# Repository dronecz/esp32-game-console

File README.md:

# ESP32 game console 

You can read more about my project [here](https://hackaday.io/project/166873-esp32-game-console) at Hackaday.io . :slightly_smiling_face:

This repository contain PCB files and 3D files for ESP32 game console. 

In case that you will have any question, you can contact me at info@czechmaker.com

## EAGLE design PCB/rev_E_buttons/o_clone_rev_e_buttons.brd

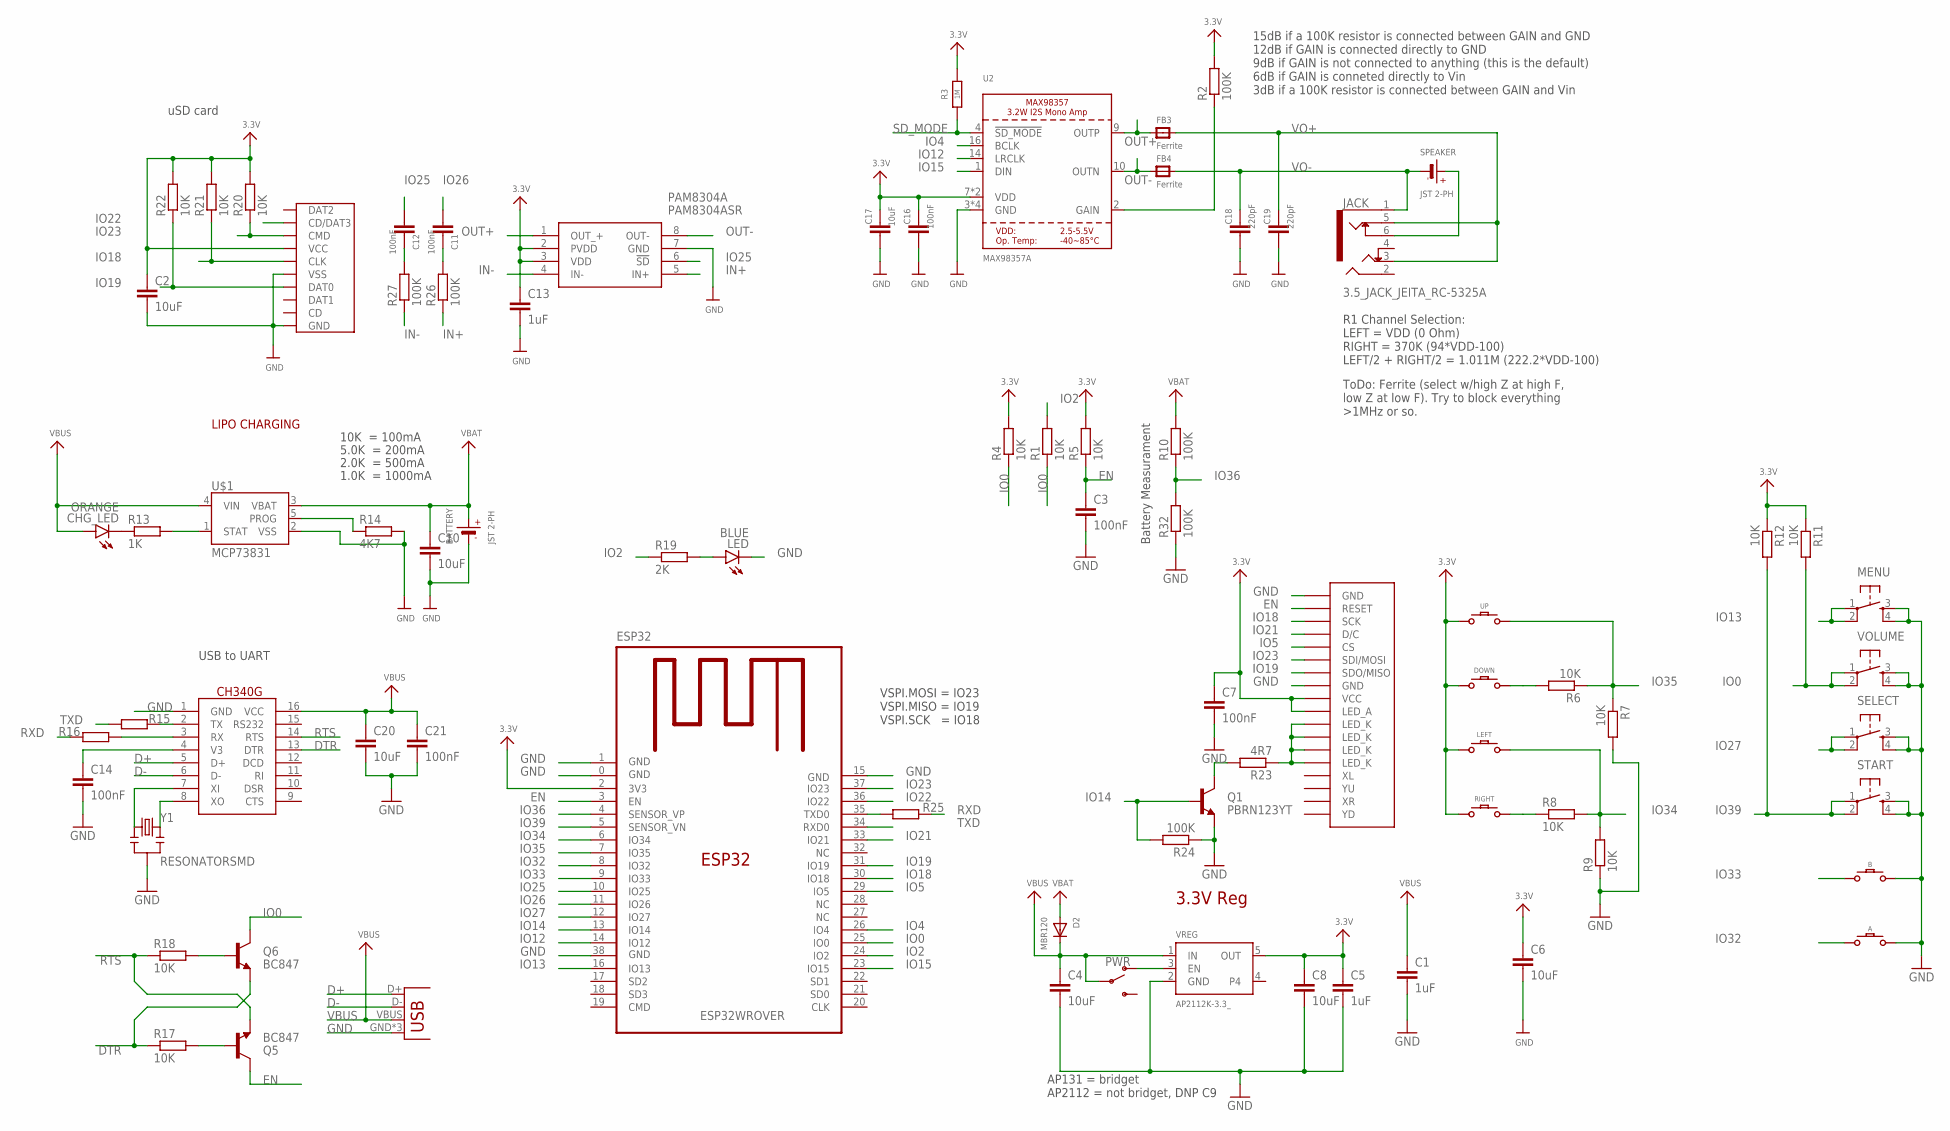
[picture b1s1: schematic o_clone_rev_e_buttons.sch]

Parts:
A: CONDUCTIVE_BUTTONCONDUCTIVE_BUTTON_THICK; CONDUCTIVE_BUTTON_THICK
B: CONDUCTIVE_BUTTONCONDUCTIVE_BUTTON_THICK; CONDUCTIVE_BUTTON_THICK
BATTERY: JST 2-PH; JSTPH2
C1, C5, C13: 1uF; C0805K
C2, C4, C6, C8, C10, C17, C20: 10uF; C0805K
C3, C11, C12, C14, C16, C21: 100nF; C0805K
C7: 100nF; C0805
C18, C19: 220pF; C0805K
CHG_LED: ORANGE; CHIPLED_0805
D2: MBR120; SOD-123
DOWN: CONDUCTIVE_BUTTONCONDUCTIVE_BUTTON_DIRECTIONAL_TH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; CONDUCTIVE_BUTTON_DIRECTIONAL_THICK
ESP32: ESP32WROVER
FB3, FB4: Ferrite; 0805
JACK: 3.5_JACK_JEITA_RC-5325A
LCD: ILI9341_3.2LCD_; LI9341_3.2LCD
LED: BLUE; CHIPLED_0805
LEFT: CONDUCTIVE_BUTTONCONDUCTIVE_BUTTON_DIRECTIONAL_TH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; CONDUCTIVE_BUTTON_DIRECTIONAL_THICK
MENU: TACTILE_SWITCHE_5X5_MICRO"; TACTILE_SWITCH_5X5_MICRO
PAM8304A: PAM8304ASR; SOP65P490X110-8N
PWR: SWITCH-SPDT-SMD-RIGHT-ANGLE; SWITCH_SPST_SMD_A
Q1: PBRN123YT; SOT23-3
Q5, Q6: BC847; SOT23-3
R1, R4, R5, R6, R7, R8, R9, R11, R12, R17, R18, R20, R21, R22: 10K; R0805
R2, R10, R24, R26, R27, R32: 100K; R0805
R3: 1M; R0805
R13: 1K; R0805
R14: 4K7; R0805
R15, R16, R25: 470R; R0805
R19: 2K; R0805
R23: 4R7; R0805
RIGHT: CONDUCTIVE_BUTTONCONDUCTIVE_BUTTON_DIRECTIONAL_TH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; CONDUCTIVE_BUTTON_DIRECTIONAL_THICK
SD_CARD: MICRO_SD_CARD"; TFP09-2--12B
SELECT: TACTILE_SWITCHE_5X5_MICRO"; TACTILE_SWITCH_5X5_MICRO
SPEAKER: JST 2-PH; JSTPH2
START: TACTILE_SWITCHE_5X5_MICRO"; TACTILE_SWITCH_5X5_MICRO
U2: MAX98357A; QFN16_3MM
U$1: MCP73831; SOT95P290X120-5
U$23: CH340G; SO16
UP: CONDUCTIVE_BUTTONCONDUCTIVE_BUTTON_DIRECTIONAL_TH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; CONDUCTIVE_BUTTON_DIRECTIONAL_THICK
USB: USB_MICRO_ATTEND_; USB_MICRO
VOLUME: TACTILE_SWITCHE_5X5_MICRO"; TACTILE_SWITCH_5X5_MICRO
VREG: AP2112K-3.3_; SOT95P290X120-5
Y1: RESONATORSMD; RESONATOR-SMD

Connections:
3.3V: C2.1, C5.1, C6.1, C7.1, C8.1, C13.1, C16.1, C17.1, DOWN.P$GND, ESP32.2 (3V3), LCD.P$9 (VCC), LCD.P$10 (LED_A), LEFT.P$GND, PAM8304A.2 (PVDD), PAM8304A.3 (VDD), R2.2, R3.2, R4.2, R5.2, R11.1, R12.1, R20.2, R21.2, R22.2, RIGHT.P$GND, SD_CARD.VCC, U2.7 (VDD), U2.8 (VDD), UP.P$GND, VREG.5 (OUT)
D+: U$23.5 (D+), USB.D+
D-: U$23.6 (D-), USB.D-
DTR: Q6.2 (E), R17.1, U$23.13 (DTR)
EN: C3.1, ESP32.3 (EN), LCD.P$2 (RESET), Q5.3 (C), R5.1
GND: A.P$ACTIVE, B.P$ACTIVE, BATTERY.1 (-), C1.2, C2.2, C3.2, C4.2, C5.2, C6.2, C7.2, C8.2, C10.2, C13.2, C14.2, C16.2, C17.2, C18.2, C19.2, C20.2, C21.2, ESP32.0 (GND), ESP32.1 (GND), ESP32.15 (GND), ESP32.38 (GND), LCD.P$1 (GND), LCD.P$8 (GND), LED.C, MENU.3, MENU.4, PAM8304A.7 (GND), Q1.2 (E), R7.2, R9.1, R14.2, R24.1, R32.1, SD_CARD.GND, SD_CARD.GND@1 (GND), SD_CARD.GND@2 (GND), SD_CARD.GND@3 (VSS), SD_CARD.VSS (GND), SELECT.3, SELECT.4, START.3, START.4, U2.3 (GND), U2.11 (GND), U2.15 (GND), U2.THERMAL (GND), U$1.2 (VSS), U$23.1 (GND), USB.GND, USB.GND@2 (GND), USB.GND@3 (GND), VOLUME.3, VOLUME.4, VREG.2 (GND), Y1.2
IN+: PAM8304A.5 (IN+), R26.1
IN-: PAM8304A.4 (IN-), R27.1
IO0: ESP32.25 (IO0), Q6.3 (C), R1.1, R4.1, R11.2, VOLUME.1, VOLUME.2
IO2: ESP32.24 (IO2), R1.2, R19.1
IO4: ESP32.26 (IO4), U2.16 (BCLK)
IO5: ESP32.29 (IO5), LCD.P$5 (CS)
IO12: ESP32.14 (IO12), U2.14 (LRCLK)
IO13: ESP32.16 (IO13), MENU.1, MENU.2
IO14: ESP32.13 (IO14), Q1.1 (B), R24.2
IO15: ESP32.23 (IO15), U2.1 (DIN)
IO18: ESP32.30 (IO18), LCD.P$3 (SCK), R21.1, SD_CARD.CLK
IO19: ESP32.31 (IO19), LCD.P$7 (SDO/MISO), R22.1, SD_CARD.DAT0
IO21: ESP32.33 (IO21), LCD.P$4 (D/C)
IO22: ESP32.36 (IO22), SD_CARD.CD/DAT3
IO23: ESP32.37 (IO23), LCD.P$6 (SDI/MOSI), R20.1, SD_CARD.CMD
IO25: C12.2, ESP32.10 (IO25), PAM8304A.6 (!SD)
IO26: C11.2, ESP32.11 (IO26)
IO27: ESP32.12 (IO27), SELECT.1, SELECT.2
IO32: A.P$GND, ESP32.8 (IO32)
IO33: B.P$GND, ESP32.9 (IO33)
IO34: ESP32.6 (IO34), LEFT.P$ACTIVE, R8.2, R9.2
IO35: ESP32.7 (IO35), R6.1, R7.1, UP.P$ACTIVE
IO36: ESP32.4 (SENSOR_VP), R10.1, R32.2
IO39: ESP32.5 (SENSOR_VN), R12.2, START.1, START.2
unnamed: ESP32.35 (TXD0), R25.2
unnamed: R8.1, RIGHT.P$ACTIVE
unnamed: PWR.1 (O), VREG.3 (EN)
unnamed: DOWN.P$ACTIVE, R6.2
unnamed: Q1.3 (C), R23.2
unnamed: LED.A, R19.2
unnamed: R2.1, U2.2 (GAIN)
unnamed: U$23.8 (XO), Y1.3
unnamed: C11.1, R26.2
unnamed: JACK.6, SPEAKER.2 (+)
unnamed: U$23.7 (XI), Y1.1
unnamed: LCD.P$11 (LED_K), LCD.P$12 (LED_K), LCD.P$13 (LED_K), LCD.P$14 (LED_K), R23.1
unnamed: CHG_LED.C, R13.1
unnamed: C12.1, R27.2
unnamed: C14.1, U$23.4 (V3)
unnamed: R15.1, U$23.2 (TX)
unnamed: R16.1, U$23.3 (RX)
unnamed: Q5.1 (B), R17.2
unnamed: Q6.1 (B), R18.2
unnamed: R13.2, U$1.1 (STAT)
unnamed: R14.1, U$1.5 (PROG)
OUT+: FB3.1, PAM8304A.1 (OUT_+), U2.9 (OUTP)
OUT-: FB4.1, PAM8304A.8 (OUT-), U2.10 (OUTN)
RTS: Q5.2 (E), R18.1, U$23.14 (RTS)
RXD: R16.2, R25.1
SD_MODE: R3.1, U2.4 (!SD_MODE)
TXD: ESP32.34 (RXD0), R15.2
VBAT: BATTERY.2 (+), C10.1, D2.A, R10.2, U$1.3 (VBAT)
VBUS: C1.1, C4.1, C20.1, C21.1, CHG_LED.A, D2.C, PWR.2, U$1.4 (VIN), U$23.16 (VCC), USB.VBUS, VREG.1 (IN)
VO+: C19.1, FB3.2, JACK.3, JACK.5
VO-: C18.1, FB4.2, JACK.1, SPEAKER.1 (-)

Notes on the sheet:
10K = 100mA
5.0K = 200mA
2.0K = 500mA
1.0K = 1000mA
LIPO CHARGING
USB to UART
Battery Measurament
3.3V Reg
uSD card
VSPI.MOSI = IO23 VSPI.MISO = IO19 VSPI.SCK = IO18
AP131 = bridget AP2112 = not bridget, DNP C9
R1 Channel Selection: LEFT = VDD (0 Ohm) RIGHT = 370K (94*VDD-100) LEFT/2 + RIGHT/2 = 1.011M (222.2*VDD-100)
ToDo: Ferrite (select w/high Z at high F, low Z at low F). Try to block everything >1MHz or so.
15dB if a 100K resistor is connected between GAIN and GND 12dB if GAIN is connected directly to GND 9dB if GAIN is not connected to anything (this is the default) 6dB if GAIN is conneted directly to Vin 3dB if a 100K resistor is connected between GAIN and Vin

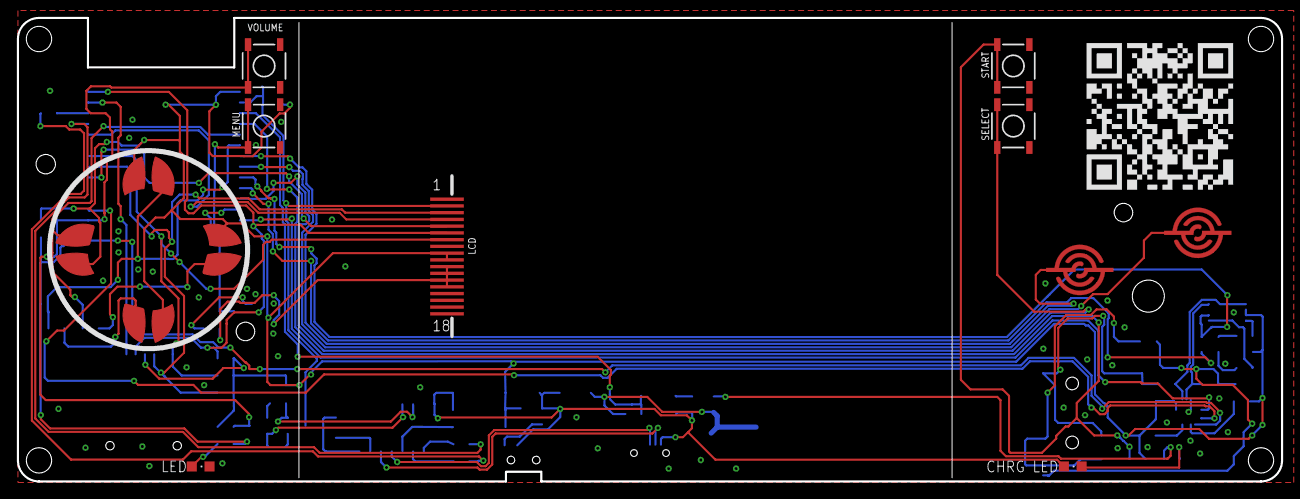
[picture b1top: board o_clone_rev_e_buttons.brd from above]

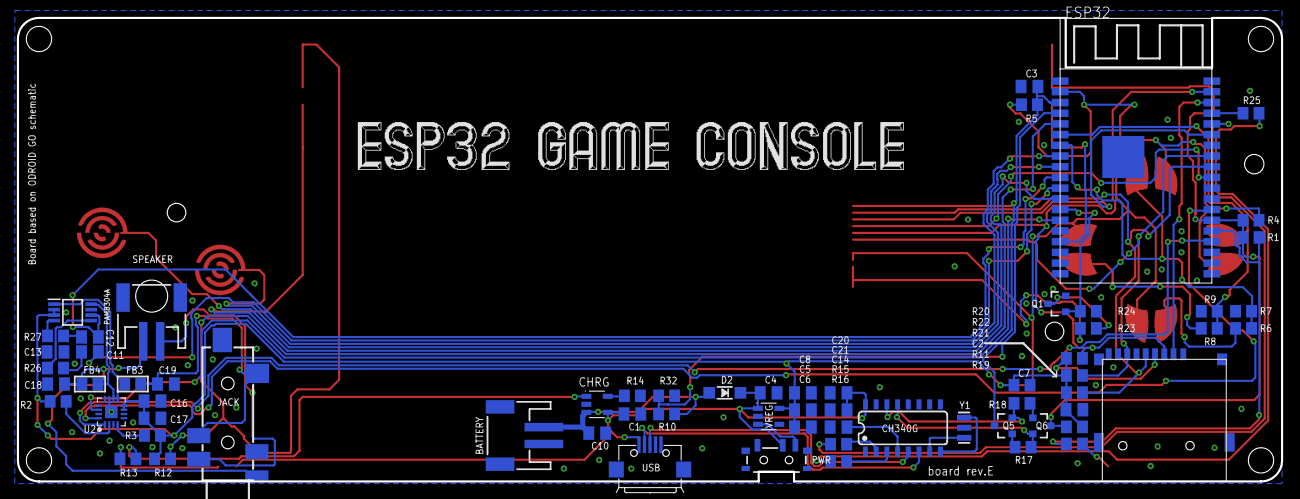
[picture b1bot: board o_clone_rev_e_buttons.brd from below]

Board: 2 copper layers, 150.0 x 55.0 mm, 79 parts (66 on the bottom side), 61 nets.

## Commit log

2020-05-28 Initial commit
    - PCB files (all versions)
    - 3D files (rev. F)
2021-03-20 Update
    - added 3mf file for PrusaSlicer with all parts
    - redesigned case and changed files to the latest design

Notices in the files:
parts and their libraries:
microbuilder: This work is placed in the public domain, and may be freely used for commercial and non-commercial work with the following conditions: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
